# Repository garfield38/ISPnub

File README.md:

# ISPnub
Firmware for stand-alone AVR programmer module

Based on the work from Thomas Fischl, the v1.1 release intergrate a 1 cell Li-ion / LiPo battery connector and a 3.3 LDO regulator.

The v1.1 release intergrate a CR2032 battery holder. Li-ion cell can be find at [Deal Extreme](http://www.dx.com/p/lir2032-rechargeable-lir2032-40mah-3-6v-lithium-cell-button-battery-silver-5-pcs-269979)

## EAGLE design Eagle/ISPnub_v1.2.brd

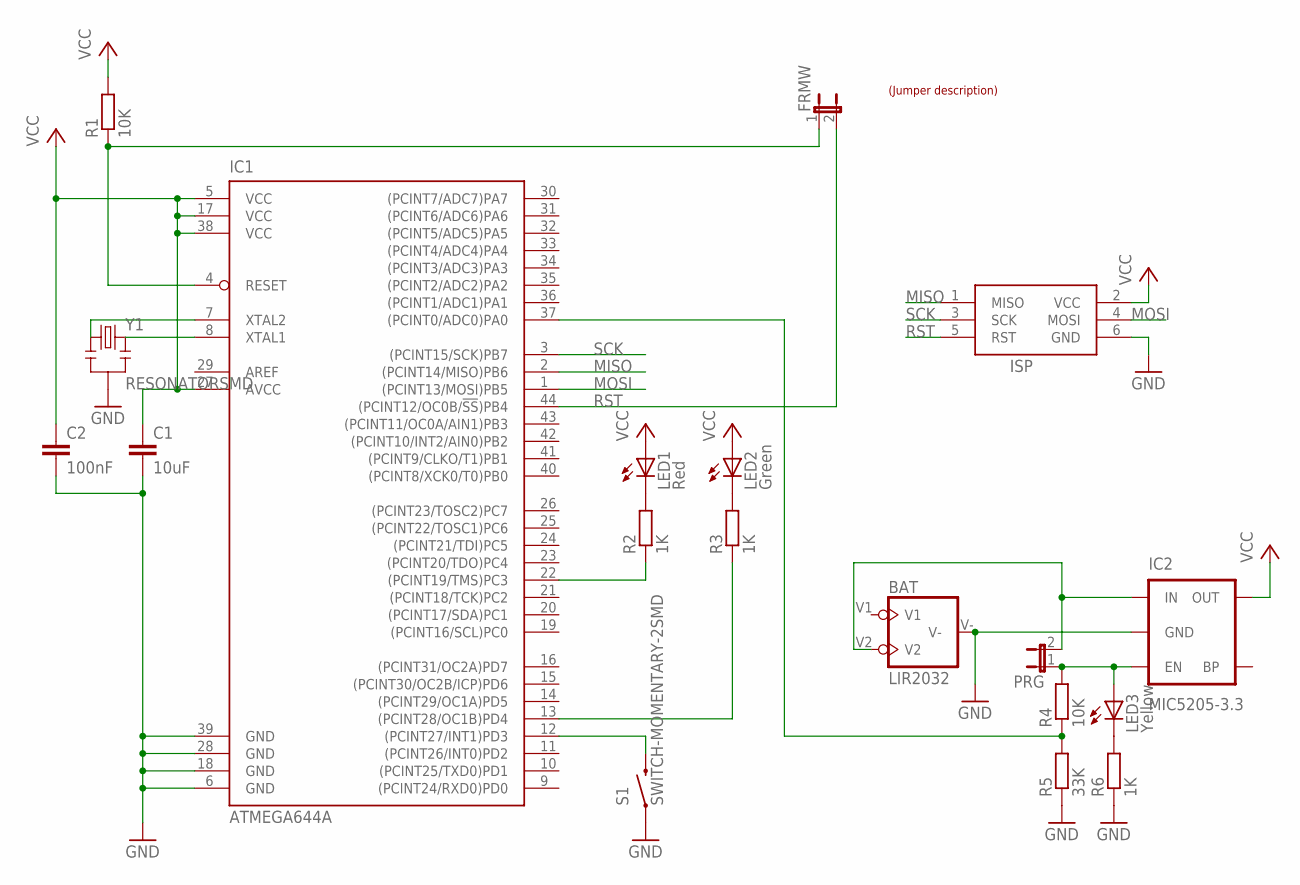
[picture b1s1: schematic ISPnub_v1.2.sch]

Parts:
BAT: LIR2032; BATT2032
C1: 10uF; C0805; MOUSER# 80-C0805C104K5R
C2: 100nF; C0805; MOUSER# 80-C0805C104K5R
FRMW: JP1E; JP1; MOUSER# 571-826936-2
IC1: ATMEGA644A; TQFP44; MOUSER# 556-ATMEGA1284P-AU
IC2: MIC5205-3.3; SOT23-5
ISP: AVRISP-6; AVRISP
LED1: Red; CHIP-LED0805; MOUSER# 604-APT1608SURC
LED2: Green; CHIP-LED0805; MOUSER# 604-APT2012SGC
LED3: Yellow; CHIP-LED0805; MOUSER# 604-APT1608YC
PRG: JP1E; JP1; MOUSER# 571-826936-2
R1: 10K; R0805; MOUSER# 603-SR0805JR-0710KL
R2, R3, R6: 1K; R0805; MOUSER# 71-CRCW0805-1.0K-E3
R4: 10K; R0402; MOUSER# 71-CRCW0805-1.0K-E3
R5: 33K; R0402; MOUSER# 71-CRCW0805-1.0K-E3
S1: SWITCH-MOMENTARY-2SMD; TACTILE_SWITCH_SMD; MOUSER# 693-1301.9314
U$1: LABEL_JUMPER_1X2; JUMP2_DESC
Y1: RESONATORSMD; RESONATOR-SMD

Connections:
GND: BAT.V-, C1.2, C2.2, IC1.6 (GND), IC1.18 (GND), IC1.28 (GND), IC1.39 (GND), IC2.2 (GND), ISP.6 (GND), R5.1, R6.1, S1.1, Y1.2
MISO: IC1.2 ((PCINT14/MISO)PB6), ISP.1 (MISO)
MOSI: IC1.1 ((PCINT13/MOSI)PB5), ISP.4 (MOSI)
unnamed: FRMW.1, IC1.4 (RESET), R1.1
unnamed: IC1.8 (XTAL1), Y1.3
unnamed: IC1.7 (XTAL2), Y1.1
unnamed: IC1.12 ((PCINT27/INT1)PD3), S1.3 (2)
unnamed: IC1.13 ((PCINT28/OC1B)PD4), R3.1
unnamed: LED2.C, R3.2
unnamed: IC1.22 ((PCINT19/TMS)PC3), R2.1
unnamed: LED1.C, R2.2
unnamed: BAT.V2, IC2.1 (IN), PRG.2
unnamed: IC2.3 (EN), LED3.A, PRG.1, R4.2
unnamed: IC1.37 ((PCINT0/ADC0)PA0), R4.1, R5.2
unnamed: LED3.C, R6.2
RST: FRMW.2, IC1.44 ((PCINT12/OC0B/!SS!)PB4), ISP.5 (RST)
SCK: IC1.3 ((PCINT15/SCK)PB7), ISP.3 (SCK)
V1: BAT.V1
VCC: C1.1, C2.1, IC1.5 (VCC), IC1.17 (VCC), IC1.27 (AVCC), IC1.38 (VCC), IC2.5 (OUT), ISP.2 (VCC), LED1.A, LED2.A, R1.2

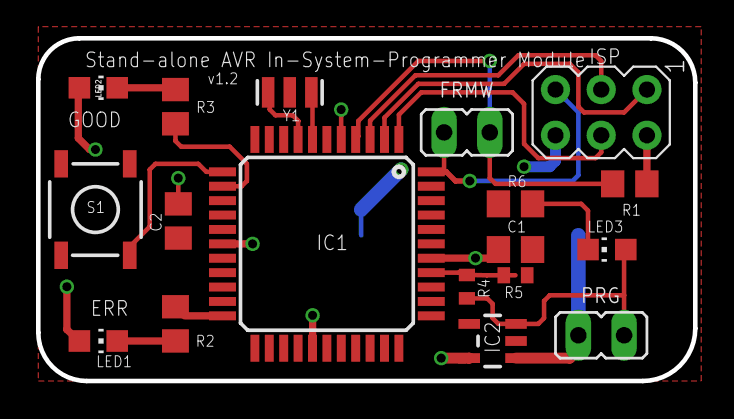
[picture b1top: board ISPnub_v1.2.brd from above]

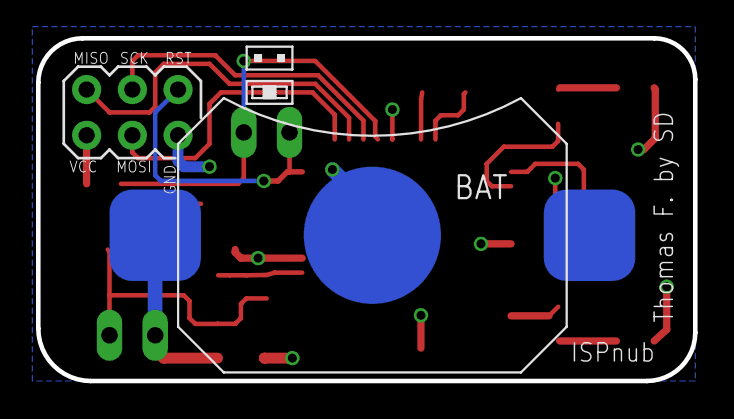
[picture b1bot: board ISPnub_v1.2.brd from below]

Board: 2 copper layers, 36.5 x 19.0 mm, 20 parts (2 on the bottom side), 18 nets.

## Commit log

2015-03-09 Add eagle files
2015-03-11 Add CR2032 Battery Holder
2015-03-11 Update README.md
    Add CR2032 battery holder option
2015-03-11 Add CR2032
